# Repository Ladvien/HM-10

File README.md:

HM-10
=====
Assortment of PCBs designed around the HM-10 BLE Serial module

A couple of programs to help, 

1. [bluetoothBehave iOS Framework](https://github.com/Ladvien/behavioralBluetooth)
2. [HM-1X Aid (Windows GUI for the HM-10 / 11)](https://github.com/Ladvien/HM-1X_Aid_v01)

[HM-10 Info](http://ladvien.github.io/robots/HM10/)

<br />This work is licensed under a <a rel="license" href="http://creativecommons.org/licenses/by-nc/4.0/">Creative Commons Attribution-NonCommercial 4.0 International License</a>.

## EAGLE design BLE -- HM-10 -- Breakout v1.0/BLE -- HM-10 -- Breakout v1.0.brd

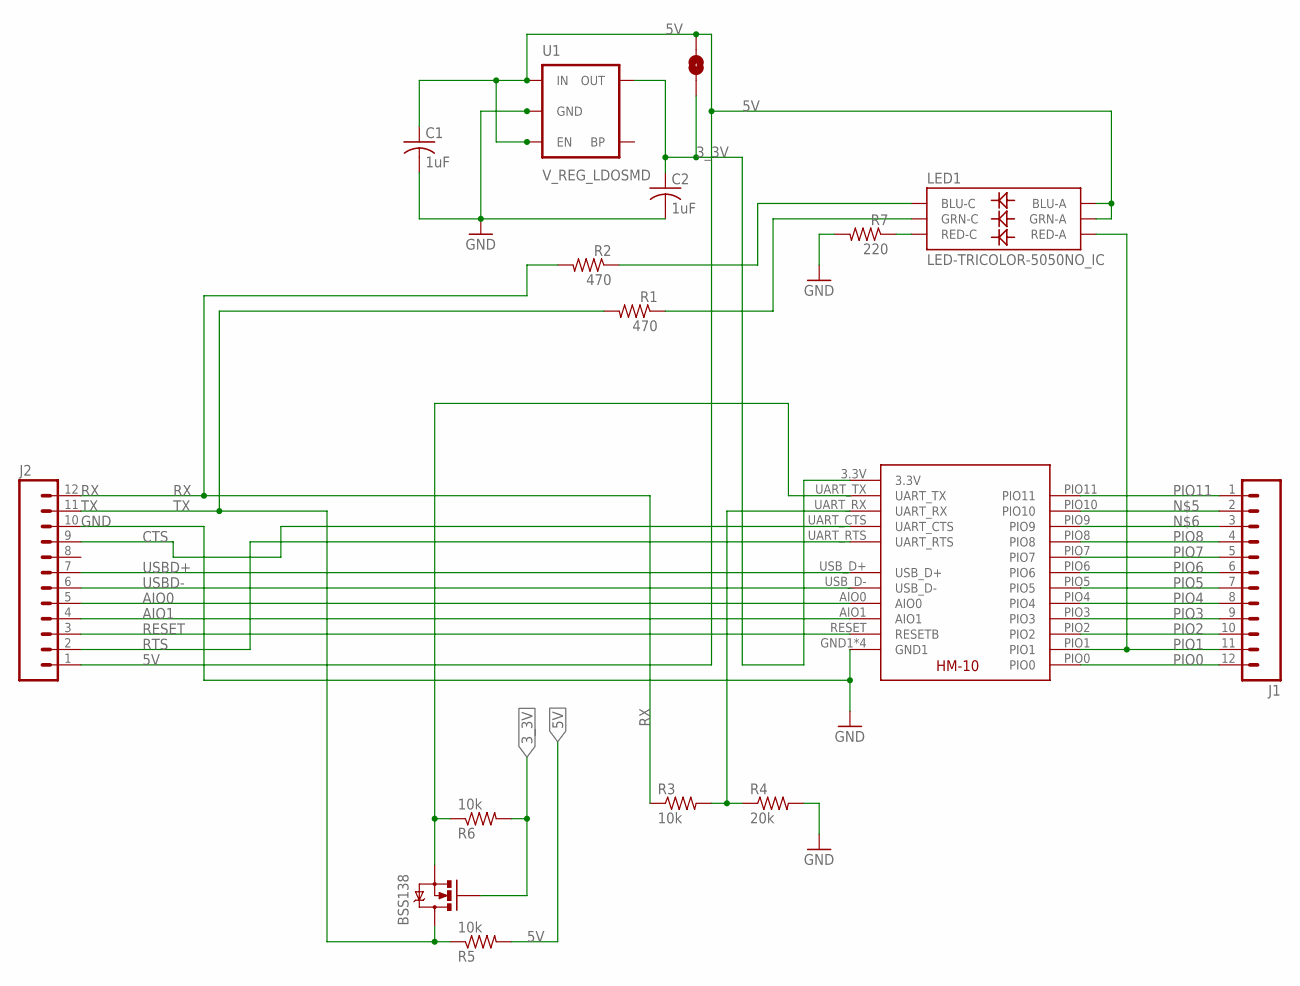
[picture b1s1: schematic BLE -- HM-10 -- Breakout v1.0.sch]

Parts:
BSS138: MOSFET-NCHANNELSMD; SOT23-3
C1, C2: 1uF; C0805K
J1, J2: M12LOCK; 1X12_LOCK
LED1: LED-TRICOLOR-5050NO_IC; LED-TRICOLOR-5050
R1, R2: 470; M0805
R3, R5, R6: 10k; M0805
R4: 20k; M0805
R7: 220; M0805
SJ1: SOLDERJUMPERNO; SJ_2S-NO
U1: V_REG_LDOSMD; SOT23-5
U$1: BLE-HM-10

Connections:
3_3V: BSS138.1 (G), C2.1, R6.2, SJ1.1, U1.5 (OUT), U$1.3.3V
5V: C1.1, J2.1, LED1.1 (GRN-A), LED1.3 (BLU-A), R5.2, SJ1.2, U1.1 (IN), U1.3 (EN)
AIO0: J2.5, U$1.AIO0
AIO1: J2.4, U$1.AIO1
CTS: J2.9, U$1.UART_CTS
GND: C1.2, C2.2, J2.10, R4.2, R7.2, U1.2 (GND), U$1.GND1, U$1.GND2 (GND1), U$1.GND3 (GND1), U$1.GND4 (GND1)
HMD_RX: R3.2, R4.1, U$1.UART_RX
unnamed: LED1.5 (RED-C), R7.1
unnamed: LED1.4 (BLU-C), R2.1
unnamed: LED1.6 (GRN-C), R1.1
unnamed: J1.2, U$1.PIO10
unnamed: J1.3, U$1.PIO9
PIO0: J1.12, U$1.PIO0
PIO1: J1.11, LED1.2 (RED-A), U$1.PIO1
PIO2: J1.10, U$1.PIO2
PIO3: J1.9, U$1.PIO3
PIO4: J1.8, U$1.PIO4
PIO5: J1.7, U$1.PIO5
PIO6: J1.6, U$1.PIO6
PIO7: J1.5, U$1.PIO7
PIO8: J1.4, U$1.PIO8
PIO11: J1.1, U$1.PIO11
RESET: J2.3, U$1.RESET (RESETB)
RTS: J2.2, U$1.UART_RTS
RX: J2.12, R2.2, R3.1
TX: BSS138.2 (S), BSS138.3 (D), J2.11, R1.2, R5.1, R6.1, U$1.UART_TX
USBD+: J2.7, U$1.USB_D+
USBD-: J2.6, U$1.USB_D-

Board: 2 copper layers, 18 parts (14 on the bottom side), 28 nets, no tracks yet.

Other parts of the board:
U$2: OSHW_FILLX350_NOTEXT
U$3: OSHW_FILLX70_NOTEXT

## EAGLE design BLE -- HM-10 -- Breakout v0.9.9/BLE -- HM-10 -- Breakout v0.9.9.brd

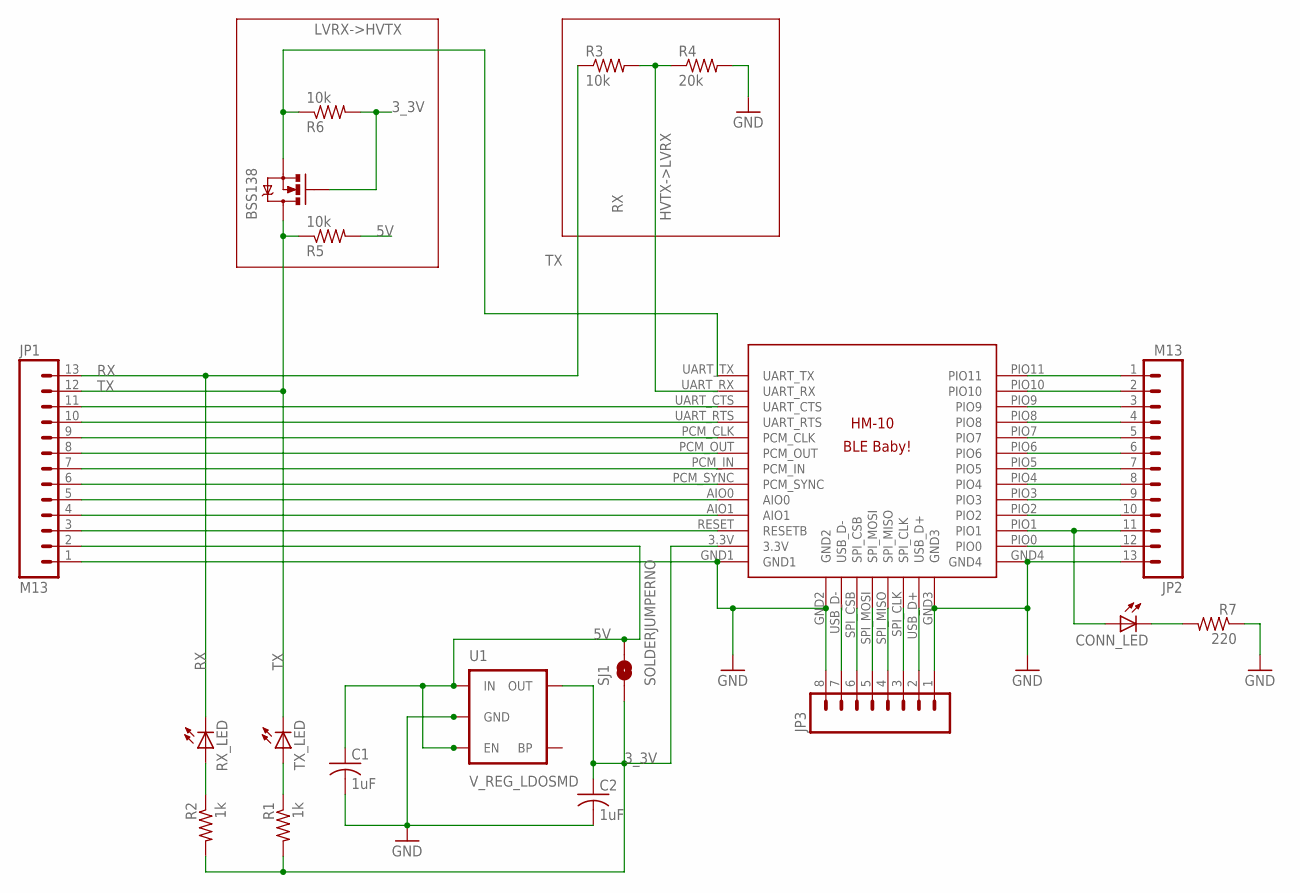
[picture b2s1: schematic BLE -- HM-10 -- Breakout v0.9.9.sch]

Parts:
BSS138: MOSFET-NCHANNELSMD; SOT23-3
C1, C2: 1uF; C0805K
CONN_LED: LED0603; LED-0603
JP1, JP2: M13; 1X13
JP3: M081X08; 1X08
R1, R2: 1k; M0805
R3, R5, R6: 10k; M0805
R4: 20k; M0805
R7: 220; M0805
RX_LED: LED0603; LED-0603
SJ1: SOLDERJUMPERNO; SJ_2S-NO
TX_LED: LED0603; LED-0603
U1: V_REG_LDOSMD; SOT23-5
U$1: BLE-HM-10

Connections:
3_3V: BSS138.1 (G), C2.1, R1.2, R2.2, R6.2, SJ1.1, U1.5 (OUT), U$1.3.3V
5V: C1.1, JP1.2, R5.2, SJ1.2, U1.1 (IN), U1.3 (EN)
GND: C1.2, C2.2, JP1.1, JP2.13, JP3.1, JP3.8, R4.2, R7.1, U1.2 (GND), U$1.GND1, U$1.GND2, U$1.GND3, U$1.GND4
HVTX->LVRX: R3.2, R4.1, U$1.UART_RX
LVRX->HVTX: BSS138.2 (S), R6.1, U$1.UART_TX
unnamed: CONN_LED.A, JP2.11, U$1.PIO1
unnamed: JP1.3, U$1.RESET (RESETB)
unnamed: JP1.4, U$1.AIO1
unnamed: JP1.5, U$1.AIO0
unnamed: JP1.6, U$1.PCM_SYNC
unnamed: JP1.7, U$1.PCM_IN
unnamed: JP1.8, U$1.PCM_OUT
unnamed: JP1.9, U$1.PCM_CLK
unnamed: JP1.10, U$1.UART_RTS
unnamed: JP1.11, U$1.UART_CTS
unnamed: JP2.1, U$1.PIO11
unnamed: JP2.2, U$1.PIO10
unnamed: JP2.3, U$1.PIO9
unnamed: JP2.4, U$1.PIO8
unnamed: JP2.5, U$1.PIO7
unnamed: JP2.6, U$1.PIO6
unnamed: JP2.7, U$1.PIO5
unnamed: JP2.8, U$1.PIO4
unnamed: JP2.9, U$1.PIO3
unnamed: JP2.10, U$1.PIO2
unnamed: R1.1, TX_LED.A
unnamed: JP2.12, U$1.PIO0
unnamed: CONN_LED.C, R7.2
unnamed: R2.1, RX_LED.A
unnamed: JP3.2, U$1.USB_D+
unnamed: JP3.3, U$1.SPI_CLK
unnamed: JP3.4, U$1.SPI_MISO
unnamed: JP3.5, U$1.SPI_MOSI
unnamed: JP3.6, U$1.SPI_CSB
unnamed: JP3.7, U$1.USB_D-
RX: JP1.13, R3.1, RX_LED.C
TX: BSS138.3 (D), JP1.12, R5.1, TX_LED.C

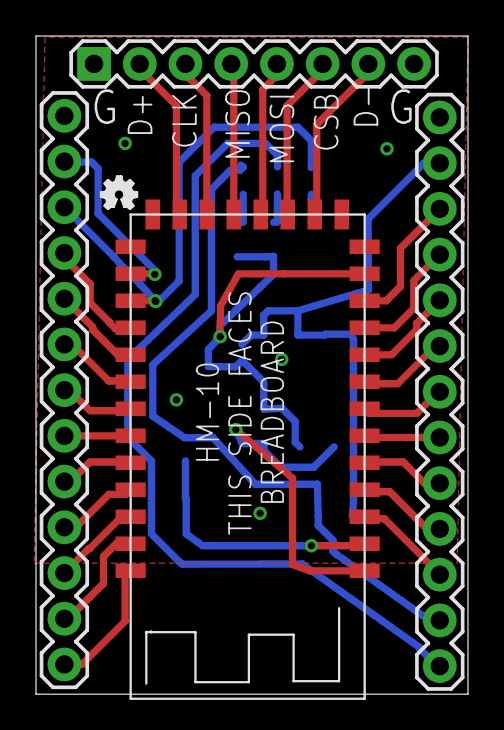
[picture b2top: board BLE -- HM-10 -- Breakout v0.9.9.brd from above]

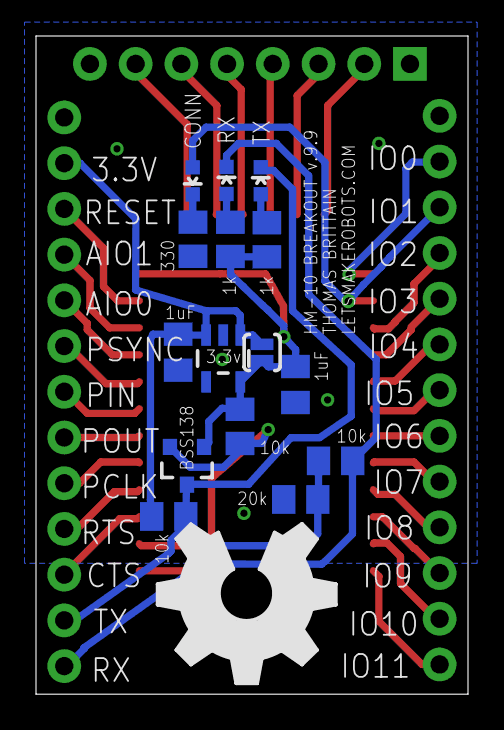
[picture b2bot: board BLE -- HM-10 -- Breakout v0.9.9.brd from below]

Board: 2 copper layers, 24.0 x 36.6 mm, 21 parts (16 on the bottom side), 37 nets.

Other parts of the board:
U$2: OSHW_FILLX350_NOTEXT
U$3: OSHW_FILLX70_NOTEXT

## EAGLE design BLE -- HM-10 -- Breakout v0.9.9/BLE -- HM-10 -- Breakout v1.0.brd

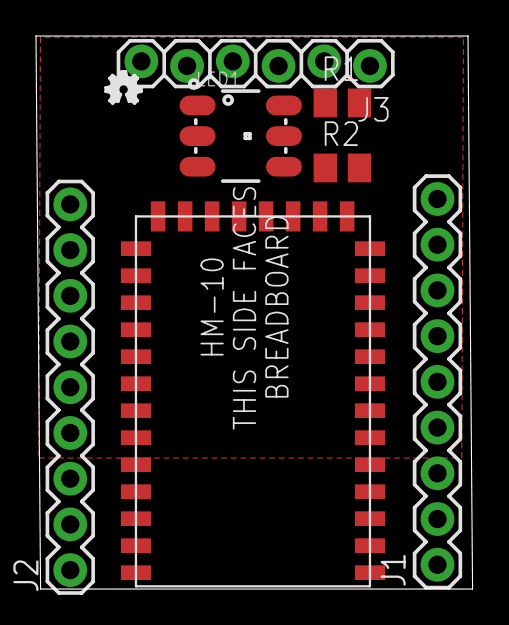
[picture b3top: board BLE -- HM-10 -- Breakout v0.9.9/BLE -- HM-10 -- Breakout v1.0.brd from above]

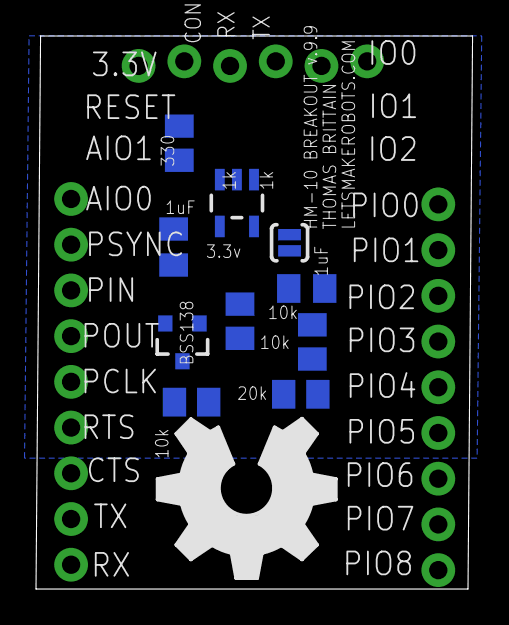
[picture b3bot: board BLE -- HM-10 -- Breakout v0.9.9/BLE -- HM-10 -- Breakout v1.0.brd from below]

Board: 2 copper layers, 24.3 x 30.7 mm, 19 parts (11 on the bottom side), 27 nets, no tracks yet.

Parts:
BSS138: MOSFET-NCHANNELSMD; SOT23-3
C1, C2: 1uF; C0805K
J1, J2: 1X09
J3: 1X06_LOCK
LED1: LED-TRICOLOR-5050NO_IC; LED-TRICOLOR-5050
R1, R2: 470; M0805
R3, R5, R6: 10k; M0805
R4: 20k; M0805
R7: 220; M0805
SJ1: SOLDERJUMPERNO; SJ_2S-NO
U1: V_REG_LDOSMD; SOT23-5
U$1: BLE-HM-10
U$2: OSHW_FILLX350_NOTEXT
U$3: OSHW_FILLX70_NOTEXT

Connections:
3_3V: BSS138.1, C2.1, R6.2, SJ1.1, U1.5, U$1.3.3V
5V: C1.1, J1.2, LED1.1, LED1.3, R5.2, SJ1.2, U1.1, U1.3
AIO0: J1.6, U$1.AIO0
AIO1: J1.5, U$1.AIO1
CTS: J3.1, U$1.UART_CTS
GND: C1.2, C2.2, J1.1, J1.3, R4.2, R7.2, U1.2, U$1.GND1, U$1.GND2, U$1.GND3, U$1.GND4
unnamed: LED1.5, R7.1
unnamed: LED1.4, R2.1
unnamed: LED1.6, R1.1
PIO0: J2.9, U$1.PIO0
PIO1: J2.8, LED1.2, U$1.PIO1
PIO2: J2.7, U$1.PIO2
PIO3: J2.6, U$1.PIO3
PIO4: J2.5, U$1.PIO4
PIO5: J2.4, U$1.PIO5
PIO6: J2.3, U$1.PIO6
PIO7: J2.2, U$1.PIO7
PIO8: J2.1, U$1.PIO8
PIO9: J3.4, U$1.PIO9
PIO10: J3.5, U$1.PIO10
PIO11: J3.6, U$1.PIO11
RESET: J1.4, U$1.RESET
RTS: J1.9, U$1.UART_RTS
RX: J3.3, R2.2, R3.1, R3.2, R4.1, U$1.UART_RX
TX: BSS138.2, BSS138.3, J3.2, R1.2, R5.1, R6.1, U$1.UART_TX
USBD+: J1.8, U$1.USB_D+
USBD-: J1.7, U$1.USB_D-

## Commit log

2013-12-27 12/26/13
2014-01-04 Added decoupling caps
2014-01-18 Deleted bad file
2014-01-18 Added corrected ATtiny Bitsy Schematic
2014-01-20 Fixed TX/RX LEDs, but untested
2014-02-06 Added v.9.9 Correct RX/TX LEDs
2014-07-06 Fixed RX/TX silkscreen error
2016-10-12 Converted to Swift 3.0
2016-10-12 Slimmed HM-10 Part -- Started smaller board
2016-10-14 Working on new v1.0
2016-10-16 2 x 12-pin connects
2017-02-17 Updating board

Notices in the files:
parts and their libraries:
SparkFun: Licensing: CC v3.0 Share-Alike You are welcome to use this library for commercial purposes.
SparkFun-Connectors: Licensing: Creative Commons ShareAlike 4.0 International - https://creativecommons.org/licenses/by-sa/4.0
